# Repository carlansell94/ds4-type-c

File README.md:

# Fork Details
This is a fork of an older version of the DS4 USB type C board, which adds screw holes to the 030 and 040 055 PCBs. These boards have also been altered to have slightly more finger-friendly corners.

The zero-ohm resistors use for matching the lengths of the data lines to the applicable connector have been removed to free up space for the screw hole.

This is based on an older version of the original board as I already had the LEDs from these older designs available, and the LED used by the newer design seems to have limited availability in the UK.

Both boards have been tested and installed in controllers.

# Original Readme

# DS4-Type-C
Hate microUSB? Looking to decrease cable clutter? This is the PS4 mod for you. This repo aims to host mostly drop-in USB Type C replacement boards for all revisions of PS4 controller. The goal for each board is to follow the USB Type C standard, and to include pads for those who wish to impedance match the USB data lines. Either solder in resistors here to compensate, or simply use a solder/wire bridge. The overall project goal is to keep all possible parts the same between boards, and to make it reasonablly easy for a person of moderate skill to populate these boards. This is an open source project though, so you're free to download [KiCad](https://www.kicad.org/download/) and start making modifications to these boards so that you can more easily populate them.

I used a 0.8mm PCB when I originally made these, and found it worked quite well. Gives a little more room to work inside the controller. Cost will likely depend on which board house you choose to go through. 

#### The Casual Coders Tindie store is now live! Head on over to [shop.casualcoders.dev](https://shop.casualcoders.dev) or [tindie.com/stores/casualcoders](https://www.tindie.com/stores/casualcoders/) (they're the same thing) if you'd like to purchase PCBs, Kits, or Pre-Assembled boards by one of us!

## Tutorial To Manufacture and assemble these boards.

# Supported boards

| DS4 Board   | Tested  | PCB                   | Connector | Led | Pictures | Credits |
|-------------|---------|-----------------------|----|--------|----------|---------|
| **JDS-001** | &#9744; | [001-011](/001%20011) | 14 | Old | [Schematic](/001%20011/001.svg), [Front](/001%20011/001_Front.png), [Back](/001%20011/001_Back.png) | [^cred001] |
| **JDS-011** | Untested - Fixed Pinout(?) | [001-011](/001%20011) | 12 | Old | [Schematic](/001%20011/001.svg), [Front](/001%20011/001_Front.png), [Back](/001%20011/001_Back.png) | [^cred011] |
| **JDS-030** | Untested - Fixed Pinout(?) | [030](/030)           | 12 | Old | [Schematic](/030/030.svg), [Front](/030/030_Front.png), [Back](/030/030_Back.png) | [^cred030] |
| **JDS-040** | &#9746; | [040-055](/040%20055) | 12 | New | [Schematic](/040%20055/040%20055.svg), [Front](/040%20055/040%20055_Front.png), [Back](/040%20055/040%20055_Back.png) | [^cred055] |
| **JDS-05X** | &#9746; | [040-055](/040%20055) | 12 | New | [Schematic](/040%20055/040%20055.svg), [Front](/040%20055/040%20055_Front.png), [Back](/040%20055/040%20055_Back.png) | [^cred055] |

[^cred001]:
    The original work for this board was done [here](https://github.com/HDR/DualShock4-USB-C) by Martin Refseth. I reworked his board to create kicad and schematic files for it. I also added compensation resistors as discussed above.
[^cred011]:
    Thanks to IcicaSora for providing the schematic for 011
[^cred030]:
    Thanks to 12brendan3 for providing the schematic for 030
[^cred055]:
    According to reddit user [u/Mcorgano](https://www.reddit.com/r/PS4Mods/comments/p2q3da/selling_dropin_replacement_type_c_charge_boards/h8oozja/) the pinout is supposedly the same between JDS-040 and JDS-055. The [idea](https://www.reddit.com/r/PS4Mods/comments/p2q3da/selling_dropin_replacement_type_c_charge_boards/h8os8rh/) for this dual board also comes from the same user.  
As of 11/08/2021, the 055 pinout has been confirmed by reddit user [u/jrmanpt](https://old.reddit.com/r/PS4Mods/comments/p6g08b/open_sourcing_the_type_c_charge_boards_help_me/hjoxedu/)
[^credresistormatching]:
    Thanks to CSab6482 in issue #4 for the suggestion to standardize the resistor numbering across all boards. Now R1/R2 are 5.1k and R3+ are 0 Ohm.
    
### Universal
The idea here is to create one "panelized" board which contains all above boards (JDS 001, 011, 030, 040, 050, 055). This means that someone could easily acquire a board for all controllers, then populate the one they need.  
Work can now begin for this panel. Though I've done enough work in March, so this will happen later.

# Parts
The goal with parts is to stay as consistent as possible between boards. Unfortunately, we have to use two types of RGB LED between the older and newer boards, but the goal is for this to be the only difference. Resistors are standardized to 0603 using the kicad hand_solder pads. We use USB type C connector C-31-M-12 to make soldering easy. Additionally, we use the Molex 530480 line of FPC connectors on all boards.  

Footprints or symbols which do not come with kicad by default are to be declared as project libraries, and included in the board directory as .pretty files. See 040 055 for as a reference.  

- New RGB LED:          [MSL0601RGBU1](https://www.mouser.com/ProductDetail/ROHM-Semiconductor/MSL0601RGBU1?qs=F5EMLAvA7IAg0rK0mfHa6w%3D%3D)
- Old RGB LED:          [MSL0104RGB](https://www.mouser.com/ProductDetail/ROHM-Semiconductor/MSL0104RGBU1?qs=%2Fha2pyFaduhThMWGX8bFHltJ8rIVfHrbMpgQU1T0g7RvDKWc6HIiGQ%3D%3D)
- USB Type C:           [Type-C-31-M-12](https://www.lcsc.com/product-detail/USB-Type-C_Korean-Hroparts-Elec-TYPE-C-31-M-12_C165948.html)
- FPC Connector - 12:   [503480-1200](https://www.mouser.com/ProductDetail/Molex/503480-1200?qs=%2Fha2pyFaduiit5JSGz5lsv1U%252BbZL3U56cNxg7eoCvCy3Ie8rHq3SFA%3D%3D)
- FPC Connector - 14:   [503480-1400](https://www.mouser.com/ProductDetail/Molex/503480-1400?qs=%2Fha2pyFadujj30aImGpM0ckpak%252BVtmx2aY5U9nBD5Hh2NWtQuUTDBg%3D%3D)
- Resistors:            [0603](https://www.mouser.com/Passive-Components/Resistors/Film-Resistors/Thin-Film-Resistors-SMD/_/N-7gz44?Keyword=0603&FS=True)
    - 2x 5.1k Ohm (Allows C to C charging) R1/R2 [All boards][^credresistormatching]
    - 2x 0 Ohm (Optional. Use for Impedance matching) R3/R4+ [All boards]

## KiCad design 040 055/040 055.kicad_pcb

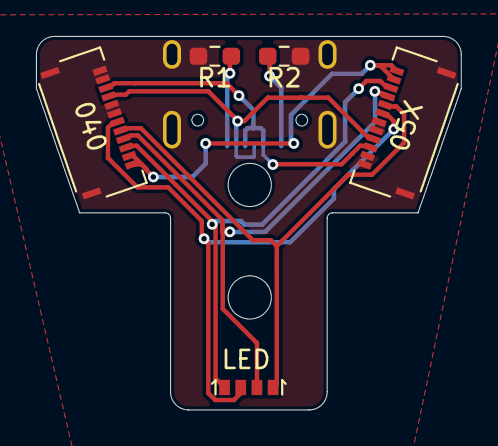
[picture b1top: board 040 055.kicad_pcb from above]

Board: 2 copper layers, 23.6 x 20.8 mm, 6 parts (1 on the bottom side), 10 nets.

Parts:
D1: LED; LED_MSL0601RGBU1
J1: USB; USB_C_Receptacle_HRO_TYPE-C-31-M-12
J2: 040; 503480-1200
J3: 05X; 503480-1200
R1, R2: 5.1k; R_0603_1608Metric_Pad0.98x0.95mm_HandSolder

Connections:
/d+: J1.A6, J1.B6
/d-: J1.A7, J1.B7
/vcc: J1.A4, J1.A9, J1.B4, J1.B9, J2.11, J2.12, J3.11, J3.12
GND: J1.A1, J1.A12, J1.B1, J1.B12, J1.S1, J2.1, J2.2, J2.5, J2.6, J2.13, J2.14, J3.1, J3.2, J3.5, J3.6, J3.13, J3.14, R1.2, R2.1
unnamed: D1.1, J2.10, J3.10
unnamed: D1.2, J2.7, J3.7
unnamed: D1.3, J2.9, J3.9
unnamed: D1.4, J2.8, J3.8
unnamed: J1.A5, R1.1
unnamed: J1.B5, R2.2

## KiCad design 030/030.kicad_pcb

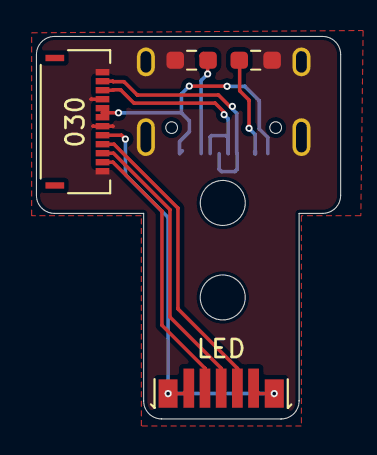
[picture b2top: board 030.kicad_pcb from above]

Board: 2 copper layers, 16.9 x 21.3 mm, 5 parts (1 on the bottom side), 10 nets.

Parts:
D1: MSL0104RGB
J1: 030; 503480-1200
R1, R2: 5.1k; R_0603_1608Metric_Pad0.98x0.95mm_HandSolder
USB: USB_C_Receptacle_USB2.0; USB_C_Receptacle_HRO_TYPE-C-31-M-12

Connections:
+5V: J1.5, J1.6, USB.A4, USB.A9, USB.B4, USB.B9
/Annode: D1.1, D1.2, D1.6, D1.7, J1.8
/B: D1.5, J1.11
/D+: J1.2, USB.A6, USB.B6
/D-: J1.3, USB.A7, USB.B7
/G: D1.3, J1.9
/R: D1.4, J1.10
GND: J1.1, J1.4, J1.7, J1.12, R1.2, R2.1, USB.A1, USB.A12, USB.B1, USB.B12, USB.S1
unnamed: R2.2, USB.A5
unnamed: R1.1, USB.B5

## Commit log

2025-08-30 Update 030 and 040 055 board to include screw mounting holes
